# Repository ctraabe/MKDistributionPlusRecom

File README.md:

# MKDistributionPlusRecom
Circuit board design for distributing the signals from the MikroKopter FlightCtrl 5-pin Molex connector, plus a RECOM SIP3 sized regulator to power an I2C peripheral (e.g. the I2C indicator).

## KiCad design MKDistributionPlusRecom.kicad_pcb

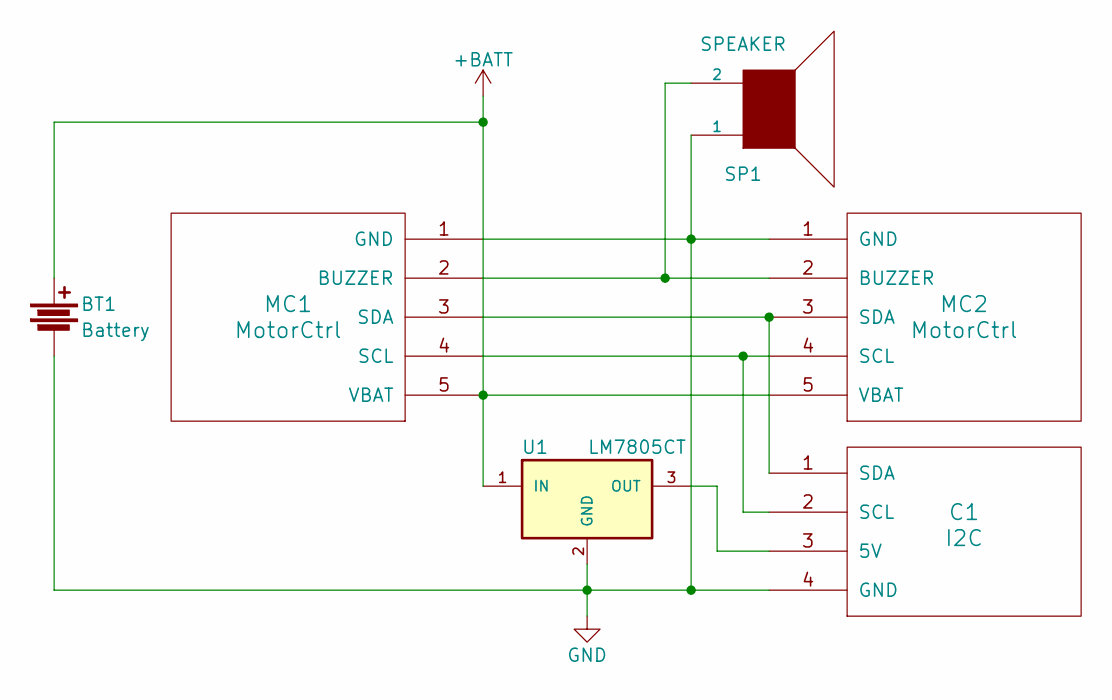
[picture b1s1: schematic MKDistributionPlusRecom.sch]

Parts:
BT1: Battery; Pin_Header_Straight_1x02
C1: I2C; Molex_PicoBlade_53047-0410_04x1.25mm_Straight
MC1, MC2: MotorCtrl; Molex_PicoBlade_53047-0510_05x1.25mm_Straight
SP1: SPEAKER; Pin_Header_Straight_1x02
U1: LM7805CT; DCDC-Conv_Recom_R-78HBxx-0.5

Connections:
+BATT: BT1.1, MC1.5 (VBAT), MC2.5 (VBAT), U1.1 (IN)
GND: BT1.2, C1.4 (GND), MC1.1 (GND), MC2.1 (GND), SP1.1, U1.2 (GND)
unnamed: C1.1 (SDA), MC1.3 (SDA), MC2.3 (SDA)
unnamed: C1.2 (SCL), MC1.4 (SCL), MC2.4 (SCL)
unnamed: C1.3 (5V), U1.3 (OUT)
unnamed: MC1.2 (BUZZER), MC2.2 (BUZZER), SP1.2

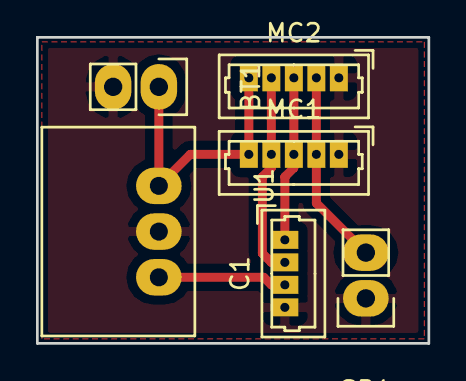
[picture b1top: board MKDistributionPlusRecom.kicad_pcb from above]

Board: 2 copper layers, 21.8 x 17.0 mm, 6 parts (0 on the bottom side), 6 nets.

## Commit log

2016-12-02 Added MikroKopter KiCad library as a submodule
2016-12-02 Committed original board version
2016-12-02 Added a second 5-pin Molex connector for BLCtrl
